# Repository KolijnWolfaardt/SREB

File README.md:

SREB
====

Stellenbosch Robotics dEvelopment Board

This board is based on the PIC18f4550 microcontroller. The board itself was designed for the Stellenbosch Robotics club, to server as a replacement for the UNO32 development board.

The circuit board and layout were done using KiCad (2013-05-18 BZR 4017)-stable. 
Additional component libraries and footprints were created using KiCad, and placed in ./lib
The Open Source Hardware logo was downloaded from http://oshwlogo.com/, and is included in ./lib

Copyright Kolijn Wolfaardt 2013.
This documentation describes Open Hardware and is licensed under the
CERN OHL v. 1.2.
You may redistribute and modify this documentation under the terms of the
CERN OHL v.1.2. (http://ohwr.org/cernohl). This documentation is distributed
WITHOUT ANY EXPRESS OR IMPLIED WARRANTY, INCLUDING OF
MERCHANTABILITY, SATISFACTORY QUALITY AND FITNESS FOR A
PARTICULAR PURPOSE. Please see the CERN OHL v.1.2 for applicable
conditions

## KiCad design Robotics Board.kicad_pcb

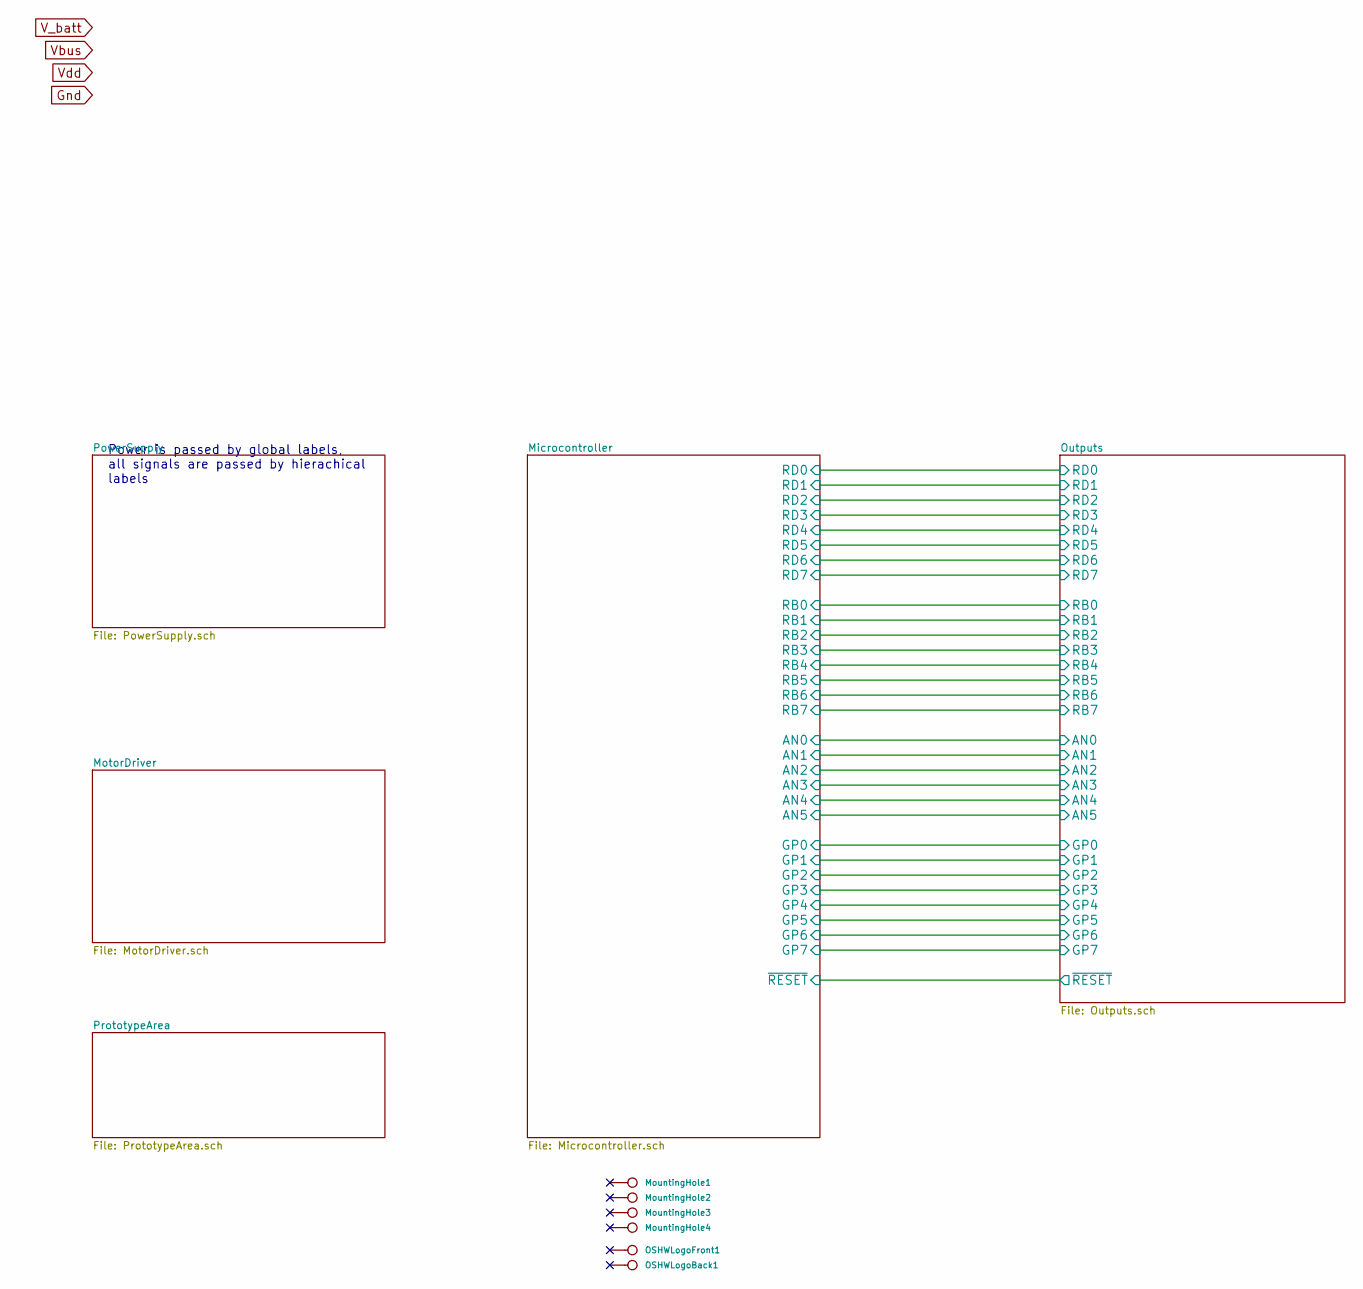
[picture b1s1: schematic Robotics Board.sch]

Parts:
MountingHole1, MountingHole2, MountingHole3, MountingHole4: CONN_1
OSHWLogoBack1: CONN_1
OSHWLogoFront1: CONN_1

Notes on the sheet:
Power is passed by global labels, all signals are passed by hierachical labels

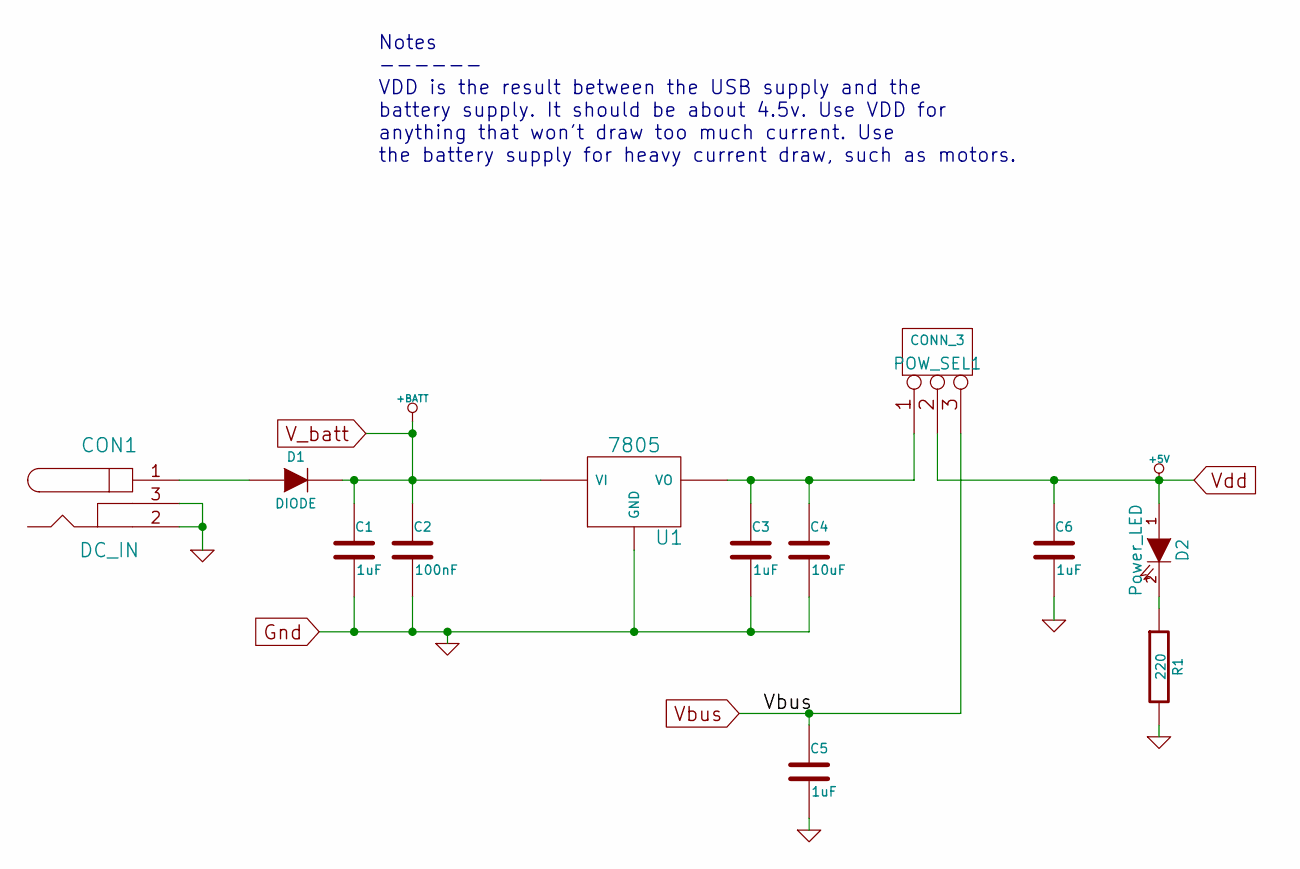
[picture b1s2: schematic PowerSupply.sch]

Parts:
C1, C3, C5, C6: 1uF
C2: 100nF
C4: 10uF
CON1: DC_IN
D1: DIODE
D2: Power_LED
POW_SEL1: CONN_3
R1: 220
U1: 7805

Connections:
Gnd: C1.2, C2.2, C3.2, C4.2, C5.2, C6.2, CON1.2, CON1.3, R1.2, U1.GND; also elsewhere on the board
unnamed: C3.1, C4.1, POW_SEL1.1, U1.VO
unnamed: D2.2 (K), R1.1
unnamed: CON1.1, D1.1 (A)
V_5v: C6.1, D2.1 (A), POW_SEL1.2 (PM); also elsewhere on the board
V_batt: C1.1, C2.1, D1.2 (K), U1.VI; also elsewhere on the board
Vbus: C5.1, POW_SEL1.3; also elsewhere on the board

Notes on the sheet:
Notes ------ VDD is the result between the USB supply and the battery supply. It should be about 4.5v. Use VDD for anything that won't draw too much current. Use the battery supply for heavy current draw, such as motors.

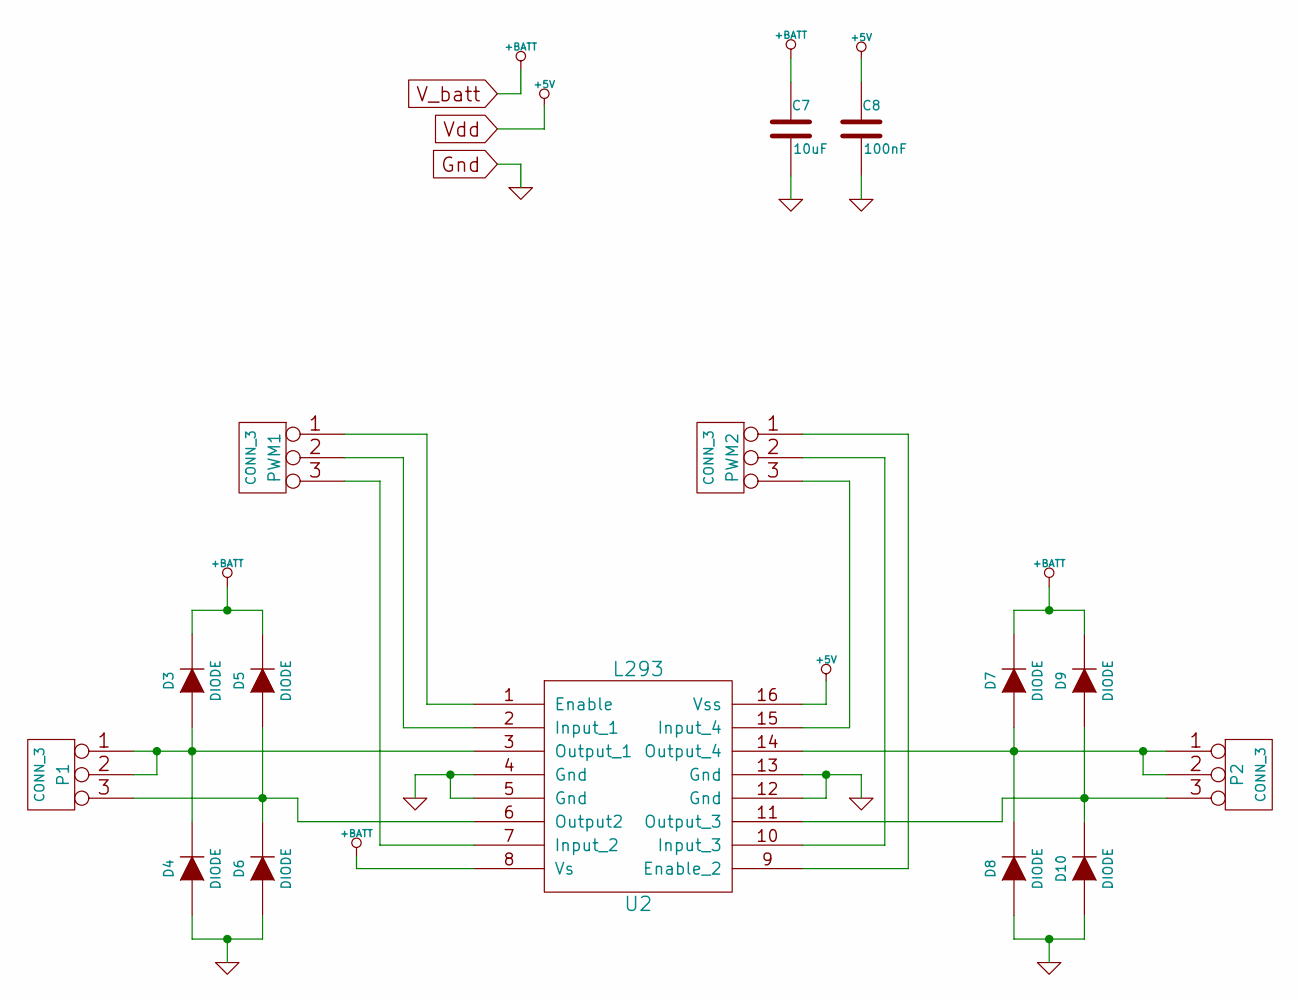
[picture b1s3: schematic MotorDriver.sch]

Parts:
C7: 10uF
C8: 100nF
D3, D4, D5, D6, D7, D8, D9, D10: DIODE
P1, P2: CONN_3
PWM1, PWM2: CONN_3
U2: L293

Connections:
Gnd: C7.2, C8.2, D4.1 (A), D6.1 (A), D8.1 (A), D10.1 (A), U2.4 (Gnd), U2.5 (Gnd), U2.12 (Gnd), U2.13 (Gnd); also elsewhere on the board
unnamed: PWM1.2 (PM), U2.2 (Input_1)
unnamed: PWM1.1, U2.1 (Enable)
unnamed: PWM2.3, U2.15 (Input_4)
unnamed: PWM2.2 (PM), U2.10 (Input_3)
unnamed: PWM1.3, U2.7 (Input_2)
unnamed: PWM2.1, U2.9 (Enable_2)
unnamed: D9.1 (A), D10.2 (K), P2.3, U2.11 (Output_3)
unnamed: D7.1 (A), D8.2 (K), P2.1, P2.2 (PM), U2.14 (Output_4)
unnamed: D3.1 (A), D4.2 (K), P1.1, P1.2 (PM), U2.3 (Output_1)
unnamed: D5.1 (A), D6.2 (K), P1.3, U2.6 (Output2)
V_5v: C8.1, U2.16 (Vss); also elsewhere on the board
V_batt: C7.1, D3.2 (K), D5.2 (K), D7.2 (K), D9.2 (K), U2.8 (Vs); also elsewhere on the board

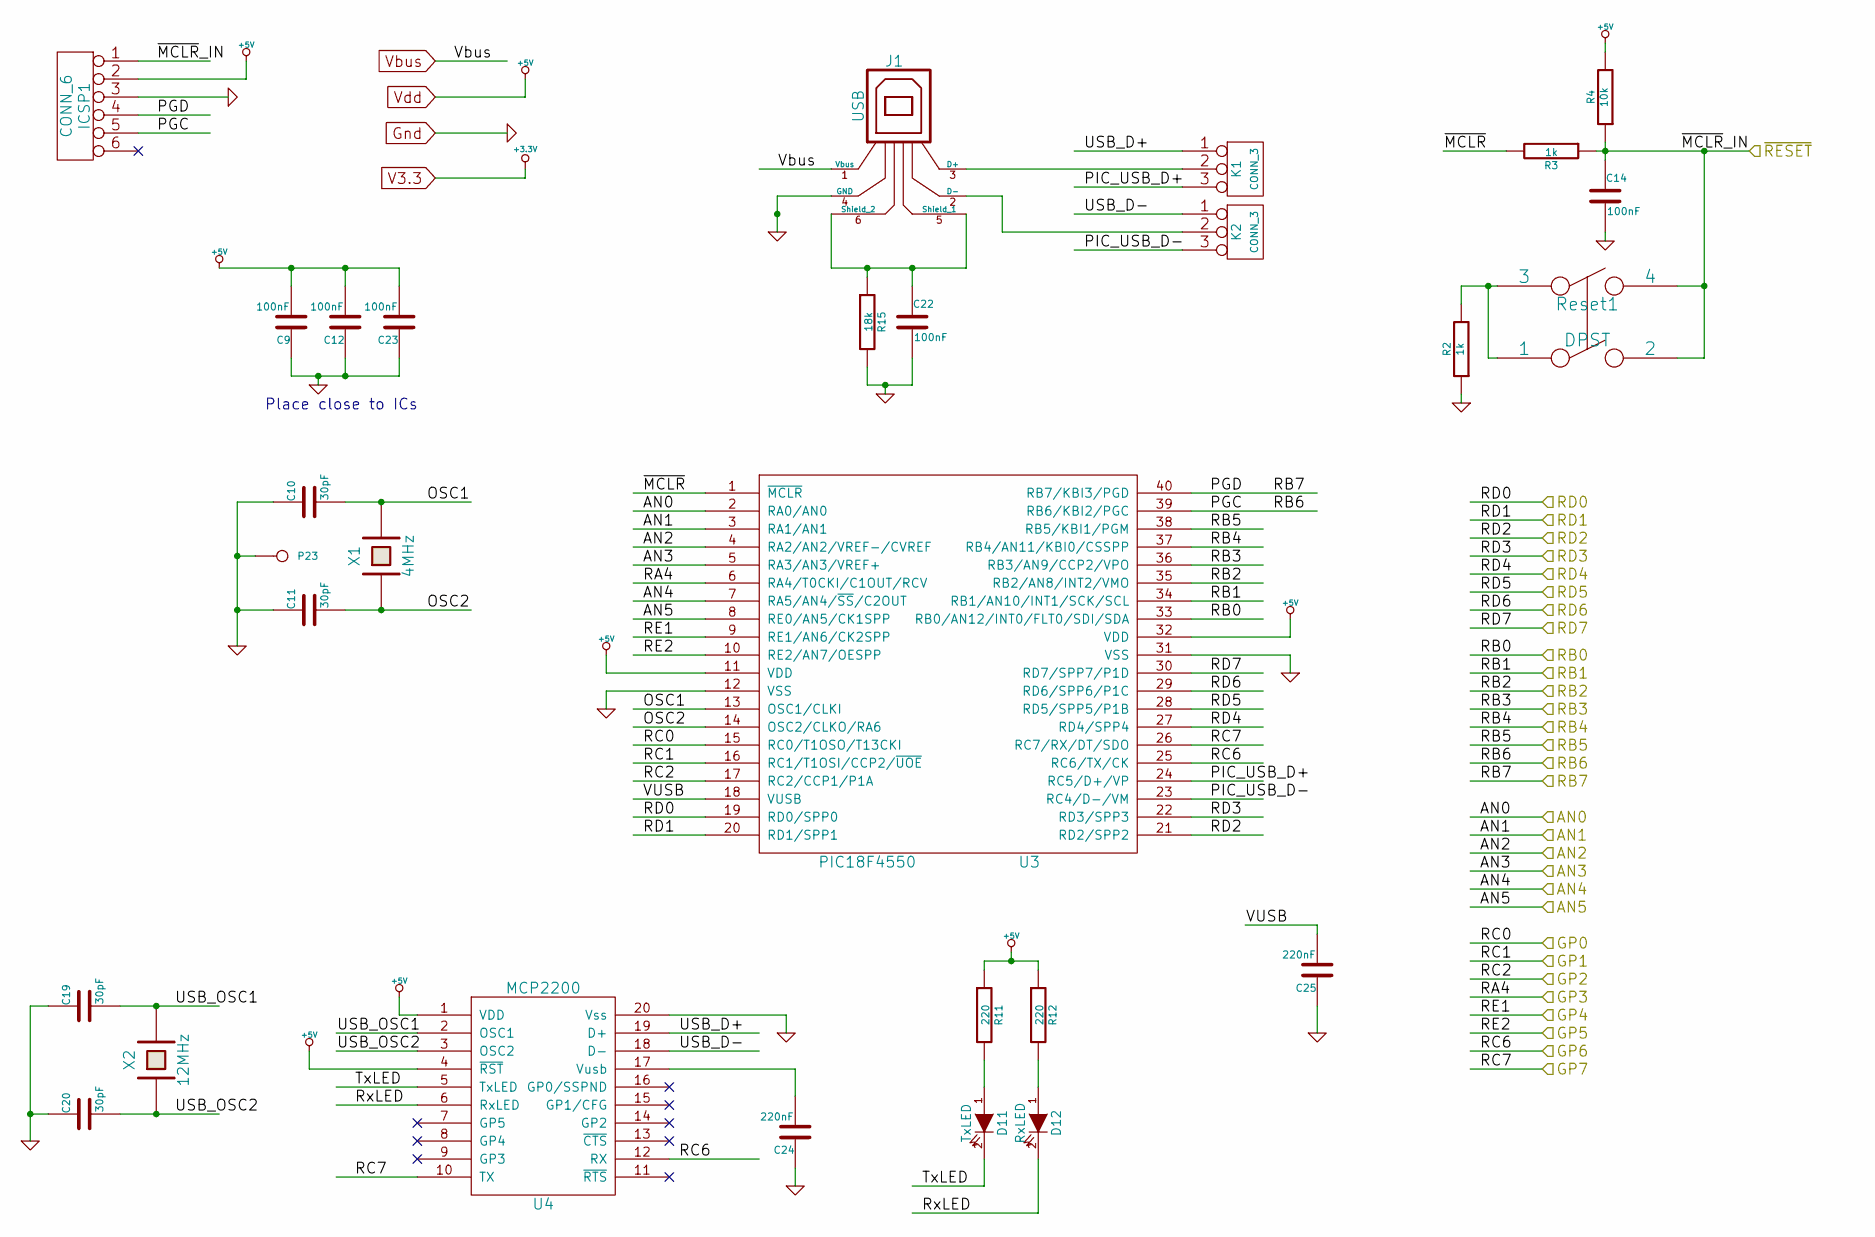
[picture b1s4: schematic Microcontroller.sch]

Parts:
C9, C12, C14, C22, C23: 100nF
C10, C11, C19, C20: 30pF
C24, C25: 220nF
D11: TxLED
D12: RxLED
ICSP1: CONN_6
J1: USB
K1, K2: CONN_3
P23: CONN_1
R2, R3: 1k
R4: 10k
R11, R12: 220
R15: 18k
Reset1: DPST
U3: PIC18F4550
U4: MCP2200
X1: 4MHz
X2: 12MHz

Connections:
/Microcontroller/AN0: U3.2 (RA0/AN0); also elsewhere on the board
/Microcontroller/AN1: U3.3 (RA1/AN1); also elsewhere on the board
/Microcontroller/AN2: U3.4 (RA2/AN2/VREF-/CVREF); also elsewhere on the board
/Microcontroller/AN3: U3.5 (RA3/AN3/VREF+); also elsewhere on the board
/Microcontroller/AN4: U3.7 (RA5/AN4/~SS~/C2OUT); also elsewhere on the board
/Microcontroller/AN5: U3.8 (RE0/AN5/CK1SPP); also elsewhere on the board
/Microcontroller/GP0: U3.15 (RC0/T1OSO/T13CKI); also elsewhere on the board
/Microcontroller/GP1: U3.16 (RC1/T1OSI/CCP2/~UOE); also elsewhere on the board
/Microcontroller/GP2: U3.17 (RC2/CCP1/P1A); also elsewhere on the board
/Microcontroller/GP3: U3.6 (RA4/T0CKI/C1OUT/RCV); also elsewhere on the board
/Microcontroller/GP4: U3.9 (RE1/AN6/CK2SPP); also elsewhere on the board
/Microcontroller/GP5: U3.10 (RE2/AN7/OESPP); also elsewhere on the board
/Microcontroller/GP6: U3.25 (RC6/TX/CK), U4.12 (RX); also elsewhere on the board
/Microcontroller/GP7: U3.26 (RC7/RX/DT/SDO), U4.10 (TX); also elsewhere on the board
/Microcontroller/OSC1: C10.2, U3.13 (OSC1/CLKI), X1.2
/Microcontroller/OSC2: C11.2, U3.14 (OSC2/CLKO/RA6), X1.1
/Microcontroller/PIC_USB_D+: K1.3, U3.24 (RC5/D+/VP)
/Microcontroller/PIC_USB_D-: K2.3, U3.23 (RC4/D-/VM)
/Microcontroller/RB0: U3.33 (RB0/AN12/INT0/FLT0/SDI/SDA); also elsewhere on the board
/Microcontroller/RB1: U3.34 (RB1/AN10/INT1/SCK/SCL); also elsewhere on the board
/Microcontroller/RB2: U3.35 (RB2/AN8/INT2/VMO); also elsewhere on the board
/Microcontroller/RB3: U3.36 (RB3/AN9/CCP2/VPO); also elsewhere on the board
/Microcontroller/RB4: U3.37 (RB4/AN11/KBI0/CSSPP); also elsewhere on the board
/Microcontroller/RB5: U3.38 (RB5/KBI1/PGM); also elsewhere on the board
/Microcontroller/RB6: ICSP1.5, U3.39 (RB6/KBI2/PGC); also elsewhere on the board
/Microcontroller/RB7: ICSP1.4, U3.40 (RB7/KBI3/PGD); also elsewhere on the board
/Microcontroller/RD0: U3.19 (RD0/SPP0); also elsewhere on the board
/Microcontroller/RD1: U3.20 (RD1/SPP1); also elsewhere on the board
/Microcontroller/RD2: U3.21 (RD2/SPP2); also elsewhere on the board
/Microcontroller/RD3: U3.22 (RD3/SPP3); also elsewhere on the board
/Microcontroller/RD4: U3.27 (RD4/SPP4); also elsewhere on the board
/Microcontroller/RD5: U3.28 (RD5/SPP5/P1B); also elsewhere on the board
/Microcontroller/RD6: U3.29 (RD6/SPP6/P1C); also elsewhere on the board
/Microcontroller/RD7: U3.30 (RD7/SPP7/P1D); also elsewhere on the board
/Microcontroller/RxLED: D12.2 (K), U4.6 (RxLED)
/Microcontroller/TxLED: D11.2 (K), U4.5 (TxLED)
/Microcontroller/USB_D+: K1.1, U4.19 (D+)
/Microcontroller/USB_D-: K2.1, U4.18 (D-)
/Microcontroller/USB_OSC1: C19.2, U4.2 (OSC1), X2.2
/Microcontroller/USB_OSC2: C20.2, U4.3 (OSC2), X2.1
/Microcontroller/VUSB: C25.2, U3.18 (VUSB)
/Microcontroller/~MCLR: R3.2, U3.1 (~MCLR)
/Microcontroller/~RESET: C14.1, ICSP1.1, R3.1, R4.1, Reset1.2, Reset1.4; also elsewhere on the board
Gnd: C9.1, C10.1, C11.1, C12.1, C14.2, C19.1, C20.1, C22.2, C23.1, C24.1, C25.1, ICSP1.3, J1.4 (GND), P23.1, R2.1, R15.2, U3.12 (VSS), U3.31 (VSS), U4.20 (Vss); also elsewhere on the board
unnamed: J1.3 (D+), K1.2 (PM)
unnamed: J1.2 (D-), K2.2 (PM)
unnamed: C22.1, J1.5 (Shield_1), J1.6 (Shield_2), R15.1
unnamed: D12.1 (A), R12.2
unnamed: D11.1 (A), R11.2
unnamed: R2.2, Reset1.1, Reset1.3
unnamed: C24.2, U4.17 (Vusb)
V_5v: C9.2, C12.2, C23.2, ICSP1.2, R4.2, R11.1, R12.1, U3.11 (VDD), U3.32 (VDD), U4.1 (VDD), U4.4 (~RST); also elsewhere on the board
Vbus: J1.1 (Vbus); also elsewhere on the board

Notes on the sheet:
Place close to ICs

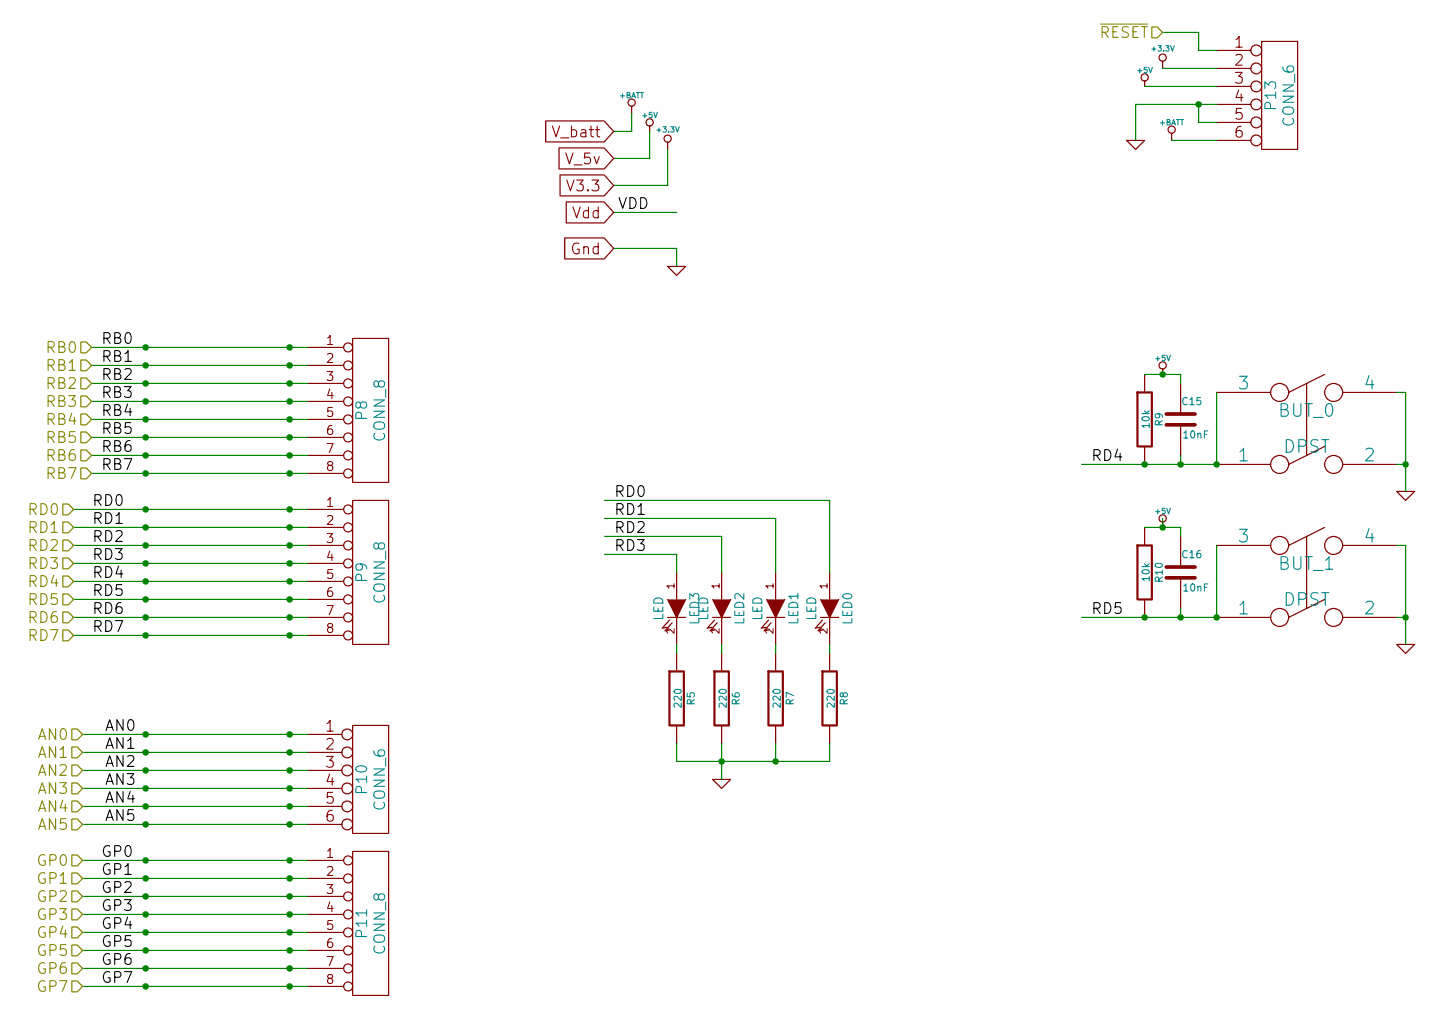
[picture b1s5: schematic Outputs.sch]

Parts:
BUT_0, BUT_1: DPST
C15, C16: 10nF
LED0, LED1, LED2, LED3: LED
P8, P9, P11: CONN_8
P10, P13: CONN_6
R5, R6, R7, R8: 220
R9, R10: 10k

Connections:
/Microcontroller/AN0: P10.1; also elsewhere on the board
/Microcontroller/AN1: P10.2; also elsewhere on the board
/Microcontroller/AN2: P10.3; also elsewhere on the board
/Microcontroller/AN3: P10.4; also elsewhere on the board
/Microcontroller/AN4: P10.5; also elsewhere on the board
/Microcontroller/AN5: P10.6; also elsewhere on the board
/Microcontroller/GP0: P11.1; also elsewhere on the board
/Microcontroller/GP1: P11.2; also elsewhere on the board
/Microcontroller/GP2: P11.3; also elsewhere on the board
/Microcontroller/GP3: P11.4; also elsewhere on the board
/Microcontroller/GP4: P11.5; also elsewhere on the board
/Microcontroller/GP5: P11.6; also elsewhere on the board
/Microcontroller/GP6: P11.7; also elsewhere on the board
/Microcontroller/GP7: P11.8; also elsewhere on the board
/Microcontroller/RB0: P8.1; also elsewhere on the board
/Microcontroller/RB1: P8.2; also elsewhere on the board
/Microcontroller/RB2: P8.3; also elsewhere on the board
/Microcontroller/RB3: P8.4; also elsewhere on the board
/Microcontroller/RB4: P8.5; also elsewhere on the board
/Microcontroller/RB5: P8.6; also elsewhere on the board
/Microcontroller/RB6: P8.7; also elsewhere on the board
/Microcontroller/RB7: P8.8; also elsewhere on the board
/Microcontroller/RD0: LED0.1 (A), P9.1; also elsewhere on the board
/Microcontroller/RD1: LED1.1 (A), P9.2; also elsewhere on the board
/Microcontroller/RD2: LED2.1 (A), P9.3; also elsewhere on the board
/Microcontroller/RD3: LED3.1 (A), P9.4; also elsewhere on the board
/Microcontroller/RD4: BUT_0.1, BUT_0.3, C15.2, P9.5, R9.2; also elsewhere on the board
/Microcontroller/RD5: BUT_1.1, BUT_1.3, C16.2, P9.6, R10.2; also elsewhere on the board
/Microcontroller/RD6: P9.7; also elsewhere on the board
/Microcontroller/RD7: P9.8; also elsewhere on the board
/Microcontroller/~RESET: P13.1; also elsewhere on the board
Gnd: BUT_0.2, BUT_0.4, BUT_1.2, BUT_1.4, P13.4, P13.5, R5.2, R6.2, R7.2, R8.2; also elsewhere on the board
unnamed: LED3.2 (K), R5.1
unnamed: LED2.2 (K), R6.1
unnamed: LED1.2 (K), R7.1
unnamed: LED0.2 (K), R8.1
V3.3: P13.2; also elsewhere on the board
V_5v: C15.1, C16.1, P13.3, R9.1, R10.1; also elsewhere on the board
V_batt: P13.6; also elsewhere on the board

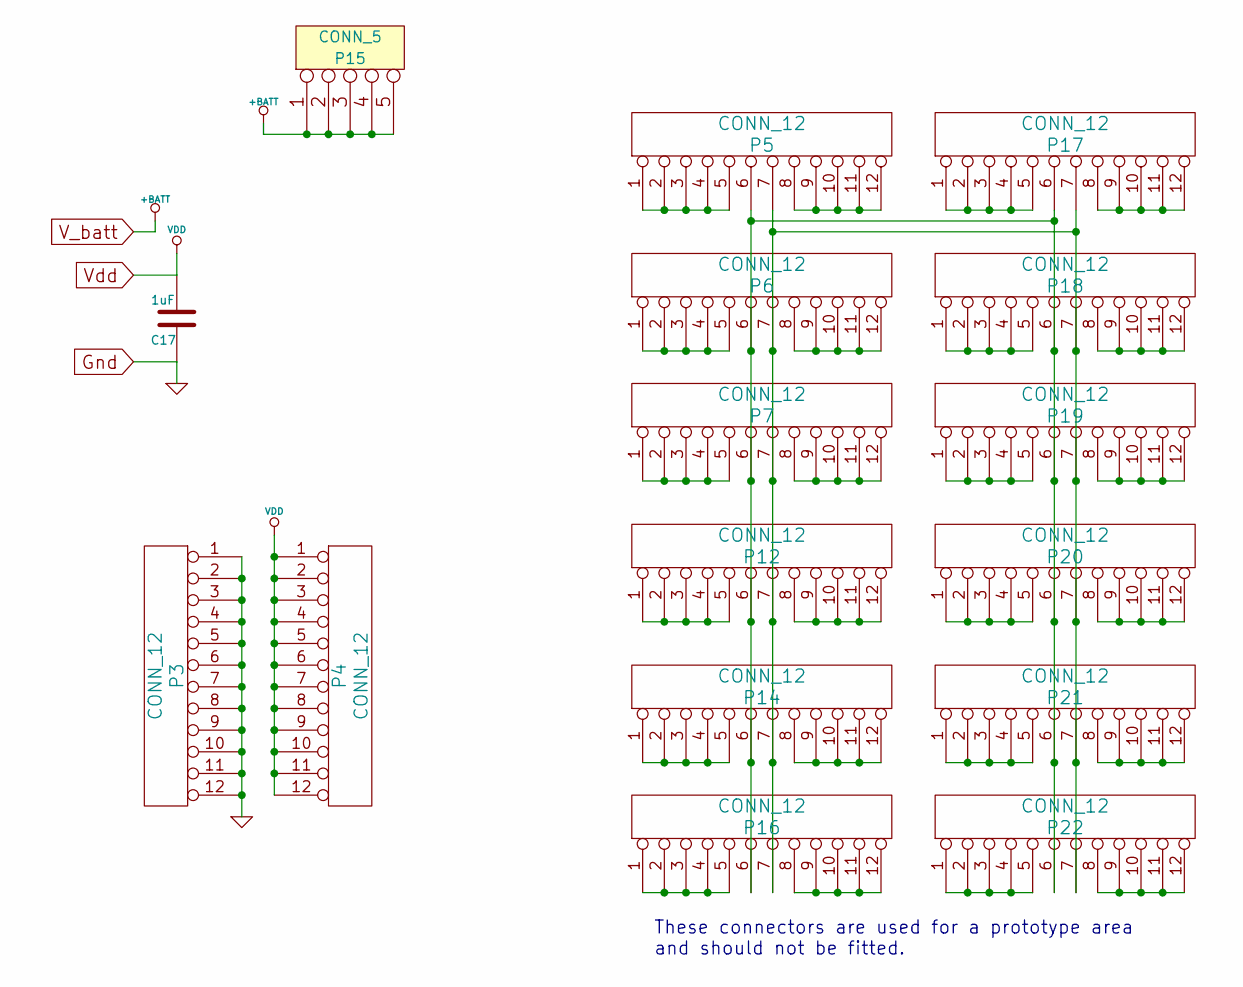
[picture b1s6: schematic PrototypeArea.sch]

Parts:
C17: 1uF
P3, P4, P5, P6, P7, P12, P14, P16, P17, P18, P19, P20, P21, P22: CONN_12
P15: CONN_5

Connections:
Gnd: C17.1, P3.1, P3.2, P3.3, P3.4, P3.5, P3.6, P3.7, P3.8, P3.9, P3.10, P3.11, P3.12; also elsewhere on the board
unnamed: P17.8, P17.9, P17.10, P17.11, P17.12
unnamed: P17.1, P17.2, P17.3, P17.4, P17.5
unnamed: P18.1, P18.2, P18.3, P18.4, P18.5
unnamed: P18.8, P18.9, P18.10, P18.11, P18.12
unnamed: P14.1, P14.2, P14.3, P14.4, P14.5
unnamed: P5.6, P6.6, P7.6, P12.6, P14.6, P16.6, P17.6, P18.6, P19.6, P20.6, P21.6, P22.6
unnamed: P14.8, P14.9, P14.10, P14.11, P14.12
unnamed: P16.1, P16.2, P16.3, P16.4, P16.5
unnamed: P16.8, P16.9, P16.10, P16.11, P16.12
unnamed: P21.1, P21.2, P21.3, P21.4, P21.5
unnamed: P21.8, P21.9, P21.10, P21.11, P21.12
unnamed: P22.1, P22.2, P22.3, P22.4, P22.5
unnamed: P22.8, P22.9, P22.10, P22.11, P22.12
unnamed: P19.1, P19.2, P19.3, P19.4, P19.5
unnamed: P19.8, P19.9, P19.10, P19.11, P19.12
unnamed: P20.1, P20.2, P20.3, P20.4, P20.5
unnamed: P20.8, P20.9, P20.10, P20.11, P20.12
unnamed: P7.1, P7.2, P7.3, P7.4, P7.5
unnamed: P7.8, P7.9, P7.10, P7.11, P7.12
unnamed: P12.1, P12.2, P12.3, P12.4, P12.5
unnamed: P5.7, P6.7, P7.7, P12.7, P14.7, P16.7, P17.7, P18.7, P19.7, P20.7, P21.7, P22.7
unnamed: P12.8, P12.9, P12.10, P12.11, P12.12
unnamed: P6.1, P6.2, P6.3, P6.4, P6.5
unnamed: P5.1, P5.2, P5.3, P5.4, P5.5
unnamed: P5.8, P5.9, P5.10, P5.11, P5.12
unnamed: P6.8, P6.9, P6.10, P6.11, P6.12
V_5v: C17.2, P4.1, P4.2, P4.3, P4.4, P4.5, P4.6, P4.7, P4.8, P4.9, P4.10, P4.11, P4.12; also elsewhere on the board
V_batt: P15.1, P15.2, P15.3, P15.4, P15.5; also elsewhere on the board

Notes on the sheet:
These connectors are used for a prototype area and should not be fitted.

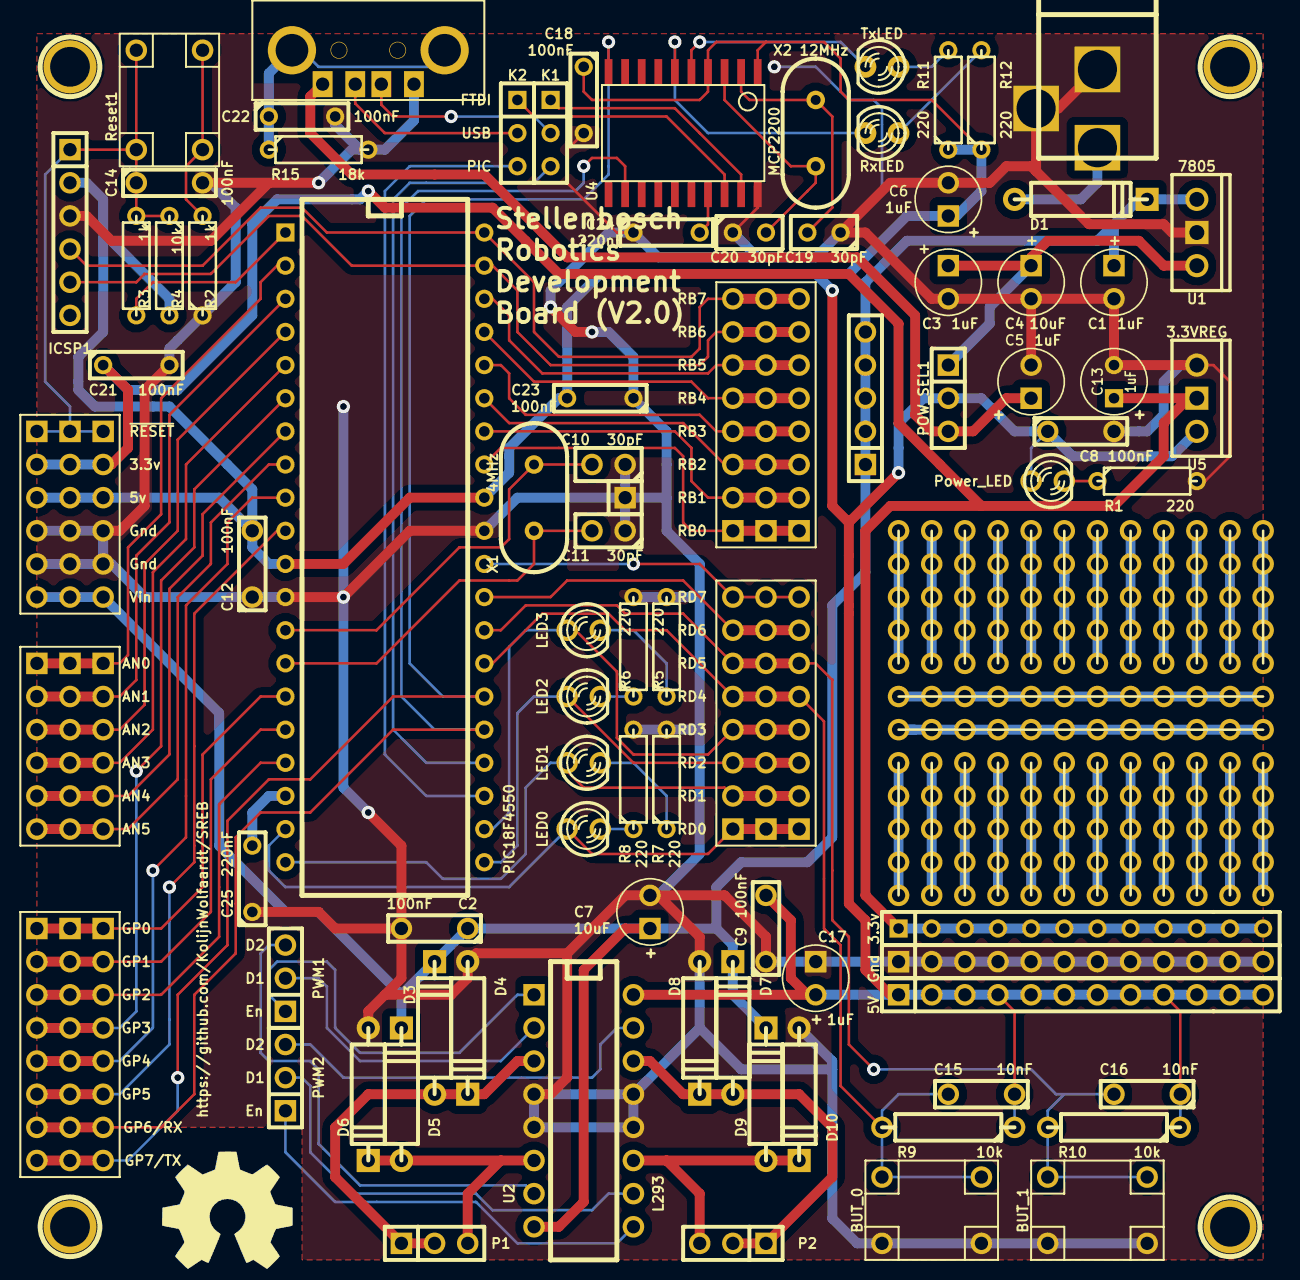
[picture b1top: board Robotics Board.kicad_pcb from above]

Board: 2 copper layers, 102 parts (1 on the bottom side), 98 nets.

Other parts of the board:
C13: 1uF; C1V5
C18, C21: 100nF; C2
P24: CONN_12; SIL-12
U5: 3.3VREG; LM78XXV-NumberedPads

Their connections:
Gnd: C13.2, C18.2, C21.2, U5.1; also elsewhere on the board
V3.3: C13.1, C21.1, P24.1, P24.2, P24.3, P24.4, P24.5, P24.6, P24.7, P24.8, P24.9, P24.10, P24.11, P24.12, U5.2; also elsewhere on the board
V_5v: C18.1, U5.3; also elsewhere on the board

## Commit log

2014-02-13 Initial commit, containing development files
2014-04-18 Changed the footprint of the PIC to the correct one. Changed the layout of the development area, to be more suited for development Changed the layout of the reset button and programmer header. The pr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
2014-04-19 Changed to FTDI chip, cut space from development area
    An FTDI chip was added to provide the USB communications rather than the PIC
    A jumper is available to choose if the USB datalines go to the FTDI chip or the
    PIC.
    The development area was reduced to provide space for the FTDI chip.
2014-04-19 Eddited USB circuit to include resistors and capacitors.
2014-04-19 Fixed some small errors
2014-04-20 Changed the board to use 3.3v rather than 5v. Total new layout.
    Since the FTDI chip cannot communicate with the 5v PIC. So run
    the PIC at 3.3v This limits the maximum crystal frequency of
    the pic, but 4MHz is fine. the internal usb regulator is no
    longer used and is replaced with the external one.
    The 3.3v regulator get it's 5v from the selected 5v source.
    5v is still used by the FTDI chip and the Motor driver.
2014-04-20 Removed unused tracks
2014-04-20 This branch uses a MCP2200 rather than an FTDI chip
2014-04-29 Not sure what I changed here
2014-04-29 Changed some silkscreen, added ground pane keepout under crystal and MCP2200
2014-04-29 Index Page Commit
2014-04-30 Changed Via size, at PCB fab's request.
2014-04-30 Initial Layout
2014-04-30 Changed Links
2014-07-20 Added the code for the bootloader.
    This is a copy of the TinyBootloader, found at
    http://www.etc.ugal.ro/cchiculita/software/picbootloader.htm
    The code was modified to work for the board using the new baud rate,
    crystal frequency and pins.
2014-07-20 Replace resistor R2 with a 0Ohm
2014-07-20 MPLABx project, containing the started code for the board.
2014-07-20 Added comments, additional testing features
2014-08-15 First Draft, hardware filled in
2014-08-19 First draft
